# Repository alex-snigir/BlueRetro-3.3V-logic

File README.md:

*Read this in other languages: [English](README_EN.md)*

# BlueRetro + Murmulator: Bluetooth-джойстики для эмулятора ретро компьютеров на перфборде

Подключение Bluetooth-геймпадов (Xbox One, PS/Switch и других HID-устройств) к эмулятору ретро компьютеров [Murmulator](https://murmulator.ru/howto) (RP2040) в качестве двух NES/Dendy-совместимых джойстиков через самодельный адаптер [BlueRetro](https://github.com/darthcloud/BlueRetro) (ESP32), выступающий мостом.

BlueRetro эмулирует на выходе стандартный протокол сдвигового регистра NES/Dendy (CLOCK/LATCH/DATA) и подключается напрямую к джойстик-портам DE-9 Мурмулятора — проводные NES-контроллеры в проекте не используются.

## Железо

- **Хост:** Murmulator (RP2040, сборка на перфборде) — VGA, PS/2-клавиатура, аудио, джойстик-порты.
- **Адаптер:** самодельный BlueRetro на ESP32 D1 mini (MH-ET LIVE, CH9102), прошивка по спецификации HW1, собственная KiCad-схема с глобальным и портовыми светодиодами статуса, входной защитой питания и вынесенной кнопкой BOOT/IO0.
- **Кабели:** JST XH 4-pin (BlueRetro) → DE-9 (Murmulator), распиновка и разводка описаны в project summary.
- **Схемы:** KiCad-проект платы BlueRetro — [`schematics/BlueRetro3V3/`](schematics/BlueRetro3V3/) (готовый PDF: [`BlueRetro3V3.pdf`](schematics/BlueRetro3V3/BlueRetro3V3.pdf)).

## Документация

| Файл | Описание |
|---|---|
| [`doc/blueretro-murmulator-project-summary.md`](doc/blueretro-murmulator-project-summary.md) / [`_EN`](doc/blueretro-murmulator-project-summary_EN.md) | Полное техническое описание: выбор платы, распиновка, питание, LED-индикация, прошивка, проверка осциллографом |
| [`doc/blueretro-murmulator-user-guide.md`](doc/blueretro-murmulator-user-guide.md) / [`_EN`](doc/blueretro-murmulator-user-guide_EN.md) | Повседневное использование: пейринг и отключение Bluetooth-геймпадов |
| [`doc/blueretro-xbox-one-nes-oscillograms.pdf`](doc/blueretro-xbox-one-nes-oscillograms.pdf) / [`_EN`](doc/blueretro-xbox-one-nes-oscillograms_EN.pdf) | Осциллограммы проверки: геймпад Xbox One как NES-джойстик — LATCH, «ничего не нажато» и поочерёдное нажатие всех 8 кнопок (исходники: [`.docx`](doc/blueretro-xbox-one-nes-oscillograms.docx) / [`_EN.docx`](doc/blueretro-xbox-one-nes-oscillograms_EN.docx); снимки — [`doc/XBox One as NES Joystick Debugging/`](<doc/XBox One as NES Joystick Debugging/>)) |
| [`murmulator-vga-project-summary.md`](https://github.com/alex-snigir/Murmulator-RP2040-Black-Perfboard-VGA/blob/master/doc/murmulator-vga-project-summary.md) / [`_EN`](https://github.com/alex-snigir/Murmulator-RP2040-Black-Perfboard-VGA/blob/master/doc/murmulator-vga-project-summary_EN.md) | Базовая сборка Мурмулятора на перфборде (хост-платформа) — отдельный репозиторий |

## Статус

Железо собрано и проверено: пейринг, работа двух портов и протокол CLOCK/LATCH/DATA подтверждены осциллографом на реальных нажатиях кнопок Xbox One.

## Благодарности

Проект основан на [BlueRetro](https://github.com/darthcloud/BlueRetro) авторства darthcloud (CERN-OHL-P-2.0 / Apache-2.0) и платформе [Murmulator](https://murmulator.ru/howto).

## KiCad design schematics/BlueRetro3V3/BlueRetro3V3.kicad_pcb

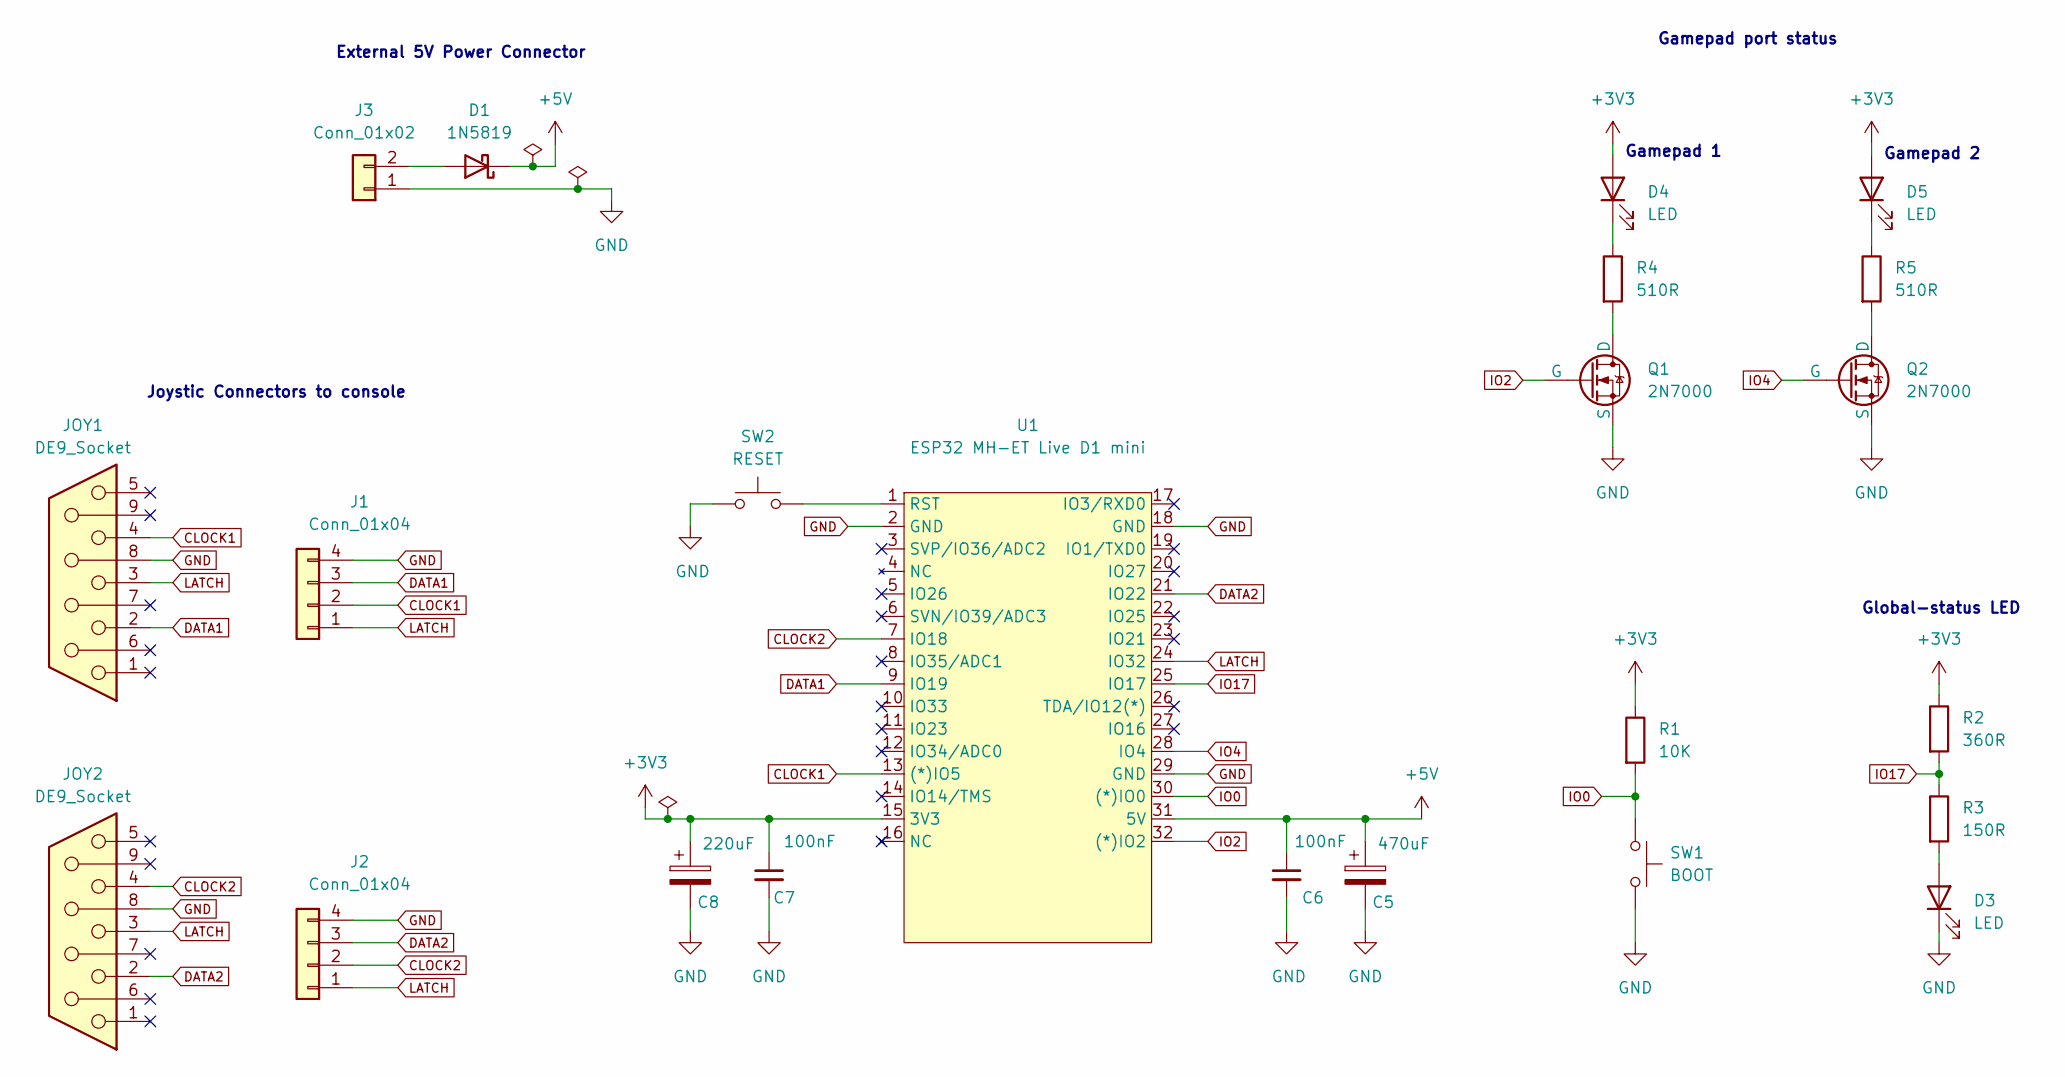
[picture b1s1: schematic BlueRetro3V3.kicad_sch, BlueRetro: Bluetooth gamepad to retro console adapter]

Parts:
C5: 470uF; CP_Radial_D8.0mm_P2.50mm
C6, C7: 100nF; C_Disc_D5.0mm_W2.5mm_P2.50mm
C8: 220uF; CP_Radial_D6.3mm_P2.50mm
D1: 1N5819; D_DO-41_SOD81_P7.62mm_Horizontal
D3, D4, D5: LED; LED_D5.0mm
J1, J2: Conn_01x04; JST_XH_S4B-XH-A_1x04_P2.50mm_Horizontal
J3: Conn_01x02; JST_XH_S2B-XH-A_1x02_P2.50mm_Horizontal
JOY1, JOY2: DE9_Socket
Q1, Q2: 2N7000; TO-92_Inline_Wide_2N7000
R1: 10K; R_Axial_DIN0207_L6.3mm_D2.2mm_P10.16mm_Horizontal
R2: 360R; R_Axial_DIN0207_L6.3mm_D2.2mm_P10.16mm_Horizontal
R3: 150R; R_Axial_DIN0207_L6.3mm_D2.2mm_P10.16mm_Horizontal
R4, R5: 510R; R_Axial_DIN0207_L6.3mm_D2.2mm_P10.16mm_Horizontal
SW1: BOOT; SW_Tactile_SKHH_Angled
SW2: RESET; SW_Tactile_SKHH_Angled
U1: ESP32 MH-ET Live D1 mini; ESP32_MH-ET_Live_D1_mini_32_pins

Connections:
+3V3: C7.1, C8.1, D4.2 (A), D5.2 (A), R1.1, R2.1, U1.15 (3V3)
+5V: C5.1, C6.1, D1.1 (K), U1.31 (5V)
CLOCK1: J1.2, JOY1.4, U1.13 ((*)IO5)
CLOCK2: J2.2, JOY2.4, U1.7 (IO18)
DATA1: J1.3, JOY1.2, U1.9 (IO19)
DATA2: J2.3, JOY2.2, U1.21 (IO22)
GND: C5.2, C6.2, C7.2, C8.2, D3.1 (K), J1.4, J2.4, J3.1, JOY1.8, JOY2.8, Q1.3 (S), Q2.3 (S), SW1.2, SW2.1, U1.2 (GND), U1.18 (GND), U1.29 (GND)
IO0: R1.2, SW1.1, U1.30 ((*)IO0)
IO2: Q1.2 (G), U1.32 ((*)IO2)
IO4: Q2.2 (G), U1.28 (IO4)
IO17: R2.2, R3.1, U1.25 (IO17)
LATCH: J1.1, J2.1, JOY1.3, JOY2.3, U1.24 (IO32)
unnamed: D1.2 (A), J3.2
unnamed: D3.2 (A), R3.2
unnamed: D4.1 (K), R4.1
unnamed: D5.1 (K), R5.1
unnamed: Q1.1 (D), R4.2
unnamed: Q2.1 (D), R5.2
unnamed: SW2.2, U1.1 (RST)

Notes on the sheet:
Joystic Connectors to console
Gamepad 2
Gamepad 1
External 5V Power Connector
Global-status LED
Gamepad port status

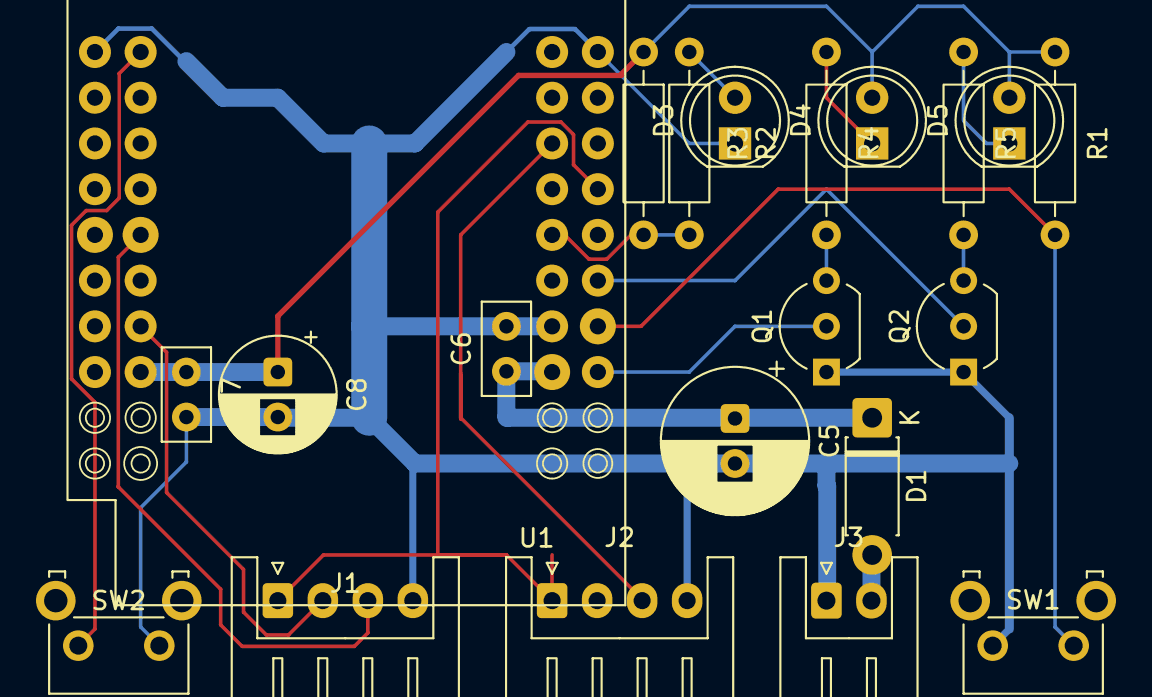
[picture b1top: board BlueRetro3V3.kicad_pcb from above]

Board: 2 copper layers, 21 parts (0 on the bottom side), 19 nets.
